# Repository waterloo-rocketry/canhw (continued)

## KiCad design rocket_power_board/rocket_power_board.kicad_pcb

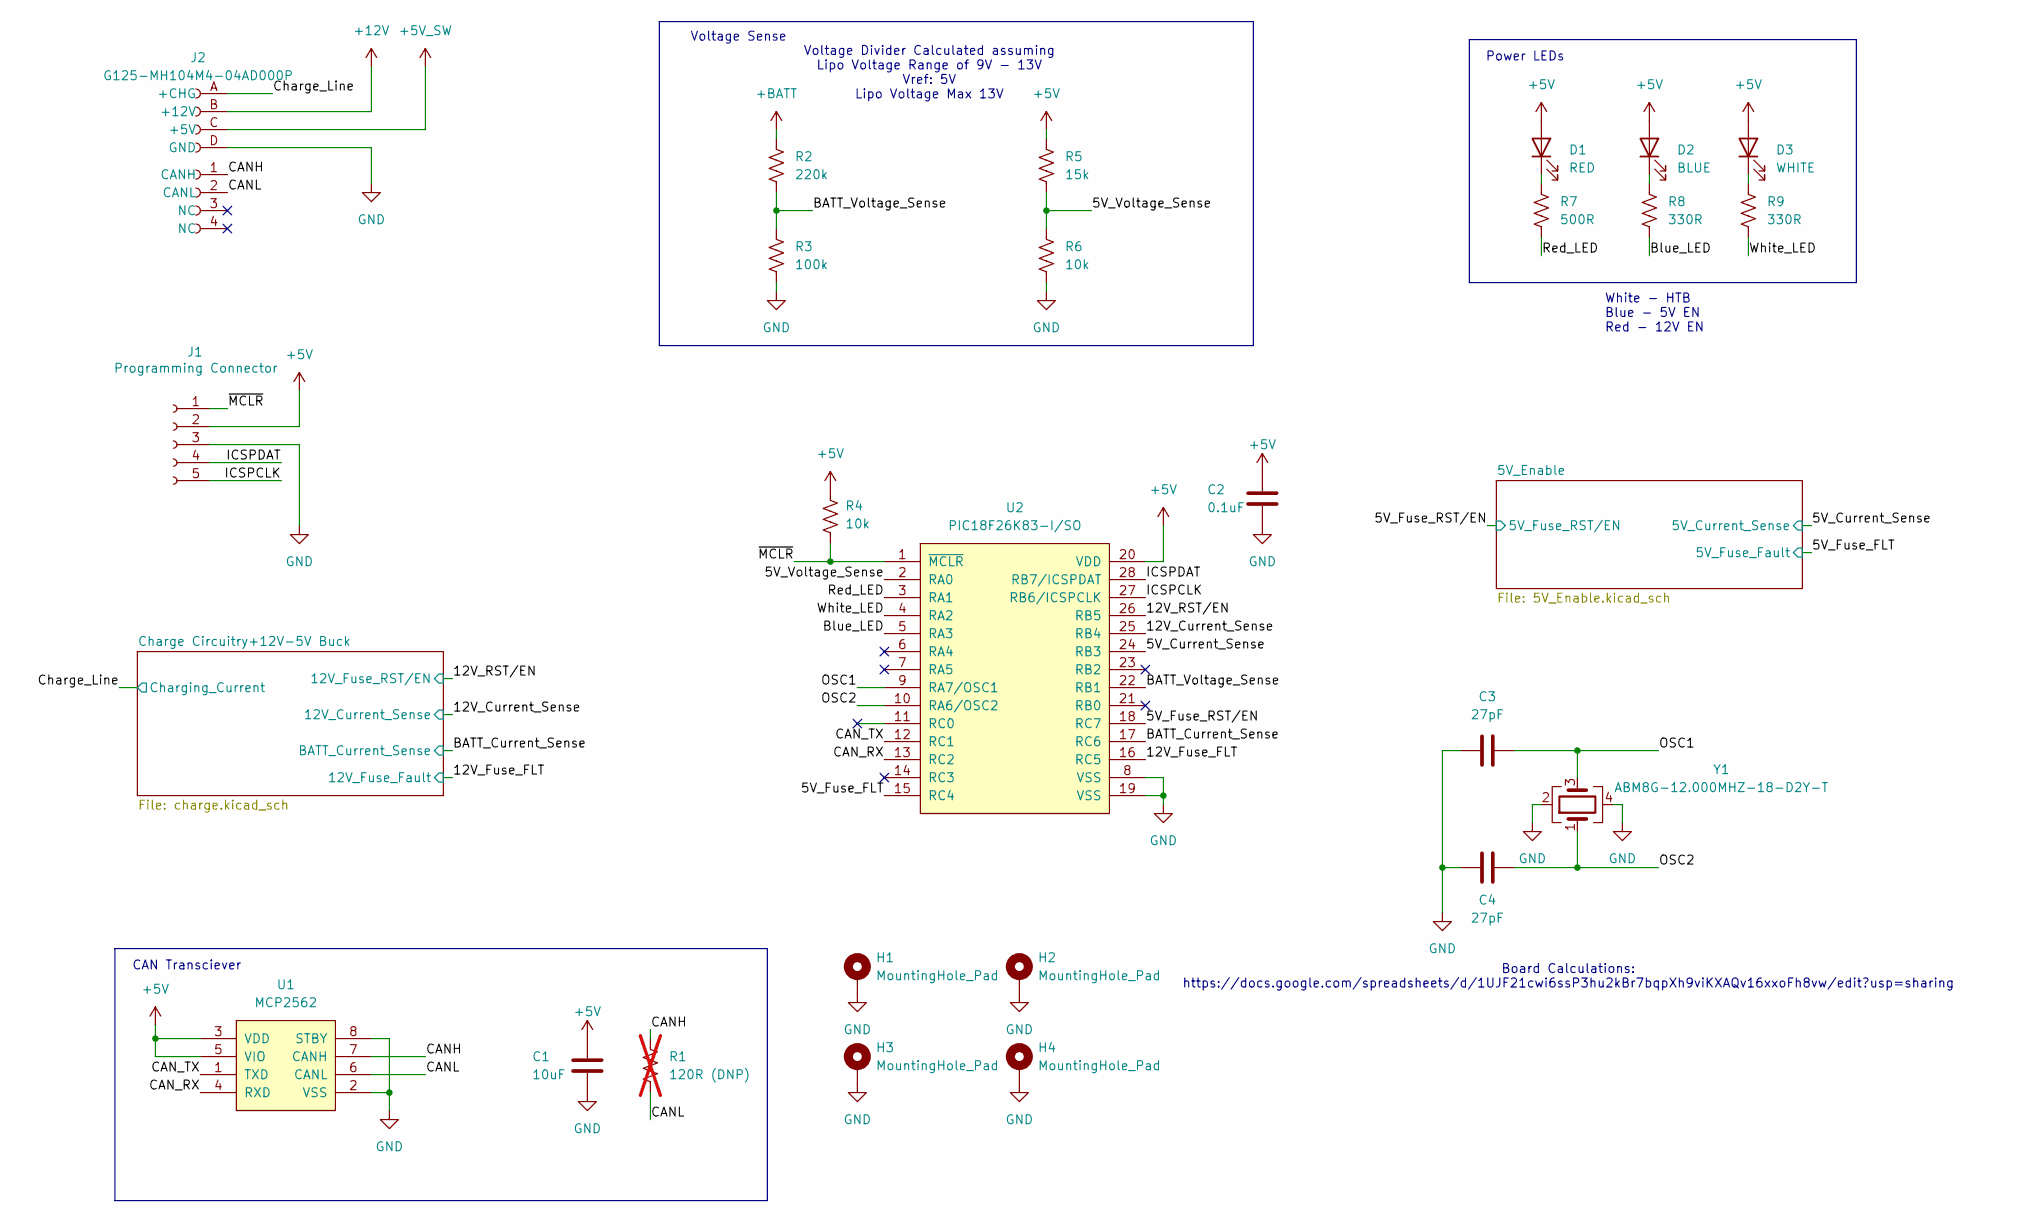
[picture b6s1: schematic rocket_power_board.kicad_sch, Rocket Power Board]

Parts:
C1: 10uF; C_0603_1608Metric_Pad1.08x0.95mm_HandSolder
C2: 0.1uF; C_0603_1608Metric_Pad1.08x0.95mm_HandSolder
C3, C4: 27pF; C_0603_1608Metric_Pad1.08x0.95mm_HandSolder
D1: RED; LED_1206_3216Metric_Pad1.42x1.75mm_HandSolder
D2: BLUE; LED_1206_3216Metric_Pad1.42x1.75mm_HandSolder
D3: WHITE; LED_1206_3216Metric_Pad1.42x1.75mm_HandSolder
H1, H2, H3, H4: MountingHole_Pad; MountingHole_3.2mm_M3_Pad_Via
J1: Programming Connector; PinSocket_5x2.54_SMD_90deg_952-3198-1-ND
J2: G125-MH104M4-04AD000P; connector_Harwin_G125-MH104M4-04AD000P
R1: 120R (DNP); R_0603_1608Metric_Pad0.98x0.95mm_HandSolder; not fitted
R2: 220k; R_0603_1608Metric_Pad0.98x0.95mm_HandSolder
R3: 100k; R_0603_1608Metric_Pad0.98x0.95mm_HandSolder
R4, R6: 10k; R_0603_1608Metric_Pad0.98x0.95mm_HandSolder
R5: 15k; R_0603_1608Metric_Pad0.98x0.95mm_HandSolder
R7: 500R; R_0603_1608Metric_Pad0.98x0.95mm_HandSolder
R8, R9: 330R; R_0603_1608Metric_Pad0.98x0.95mm_HandSolder
U1: MCP2562; SOIC-8_3.9x4.9mm_P1.27mm
U2: PIC18F26K83-I/SO; SOIC-28W_7.5x18.7mm_P1.27mm
Y1: ABM8G-12.000MHZ-18-D2Y-T; Crystal_SMD_Abracon_ABM8G-4Pin_3.2x2.5mm

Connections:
+5V: C1.1, C2.1, D1.2 (A), D2.2 (A), D3.2 (A), J1.2, R4.1, R5.1, U1.3 (VDD), U1.5 (VIO), U2.20 (VDD); also elsewhere on the board
+5V_SW: J2.C (+5V); also elsewhere on the board
+12V: J2.B (+12V); also elsewhere on the board
+BATT: R2.1; also elsewhere on the board
/5V_Current_Sense: U2.24 (RB3); also elsewhere on the board
/5V_Fuse_FLT: U2.15 (RC4); also elsewhere on the board
/5V_Fuse_RST/EN: U2.18 (RC7); also elsewhere on the board
/5V_Voltage_Sense: R5.2, R6.2, U2.2 (RA0)
/12V_Current_Sense: U2.25 (RB4); also elsewhere on the board
/12V_Fuse_FLT: U2.16 (RC5); also elsewhere on the board
/12V_RST/EN: U2.26 (RB5); also elsewhere on the board
/BATT_Current_Sense: U2.17 (RC6); also elsewhere on the board
/BATT_Voltage_Sense: R2.2, R3.2, U2.22 (RB1)
/Blue_LED: R8.2, U2.5 (RA3)
/CANH: J2.1 (CANH), R1.1, U1.7 (CANH)
/CANL: J2.2 (CANL), R1.2, U1.6 (CANL)
/CAN_RX: U1.4 (RXD), U2.13 (RC2)
/CAN_TX: U1.1 (TXD), U2.12 (RC1)
/Charge_Line: J2.A (+CHG); also elsewhere on the board
/ICSPCLK: J1.5, U2.27 (RB6/ICSPCLK)
/ICSPDAT: J1.4, U2.28 (RB7/ICSPDAT)
/OSC1: C3.2, U2.9 (RA7/OSC1), Y1.3
/OSC2: C4.2, U2.10 (RA6/OSC2), Y1.1
/Red_LED: R7.2, U2.3 (RA1)
/White_LED: R9.2, U2.4 (RA2)
/~MCLR: J1.1, R4.2, U2.1 (~MCLR)
GND: C1.2, C2.2, C3.1, C4.1, H1.1, H2.1, H3.1, H4.1, J1.3, J2.D (GND), R3.1, R6.1, U1.2 (VSS), U1.8 (STBY), U2.8 (VSS), U2.19 (VSS), Y1.2, Y1.4; also elsewhere on the board
unnamed: D1.1 (K), R7.1
unnamed: D2.1 (K), R8.1
unnamed: D3.1 (K), R9.1

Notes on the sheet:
Voltage Divider Calculated assuming Lipo Voltage Range of 9V - 13V Vref: 5V Lipo Voltage Max 13V
CAN Transciever
Board Calculations: https://docs.google.com/spreadsheets/d/1UJF21cwi6ssP3hu2kBr7bqpXh9viKXAQv16xxoFh8vw/edit?usp=sharing
White - HTB Blue - 5V EN Red - 12V EN
Power LEDs
Voltage Sense

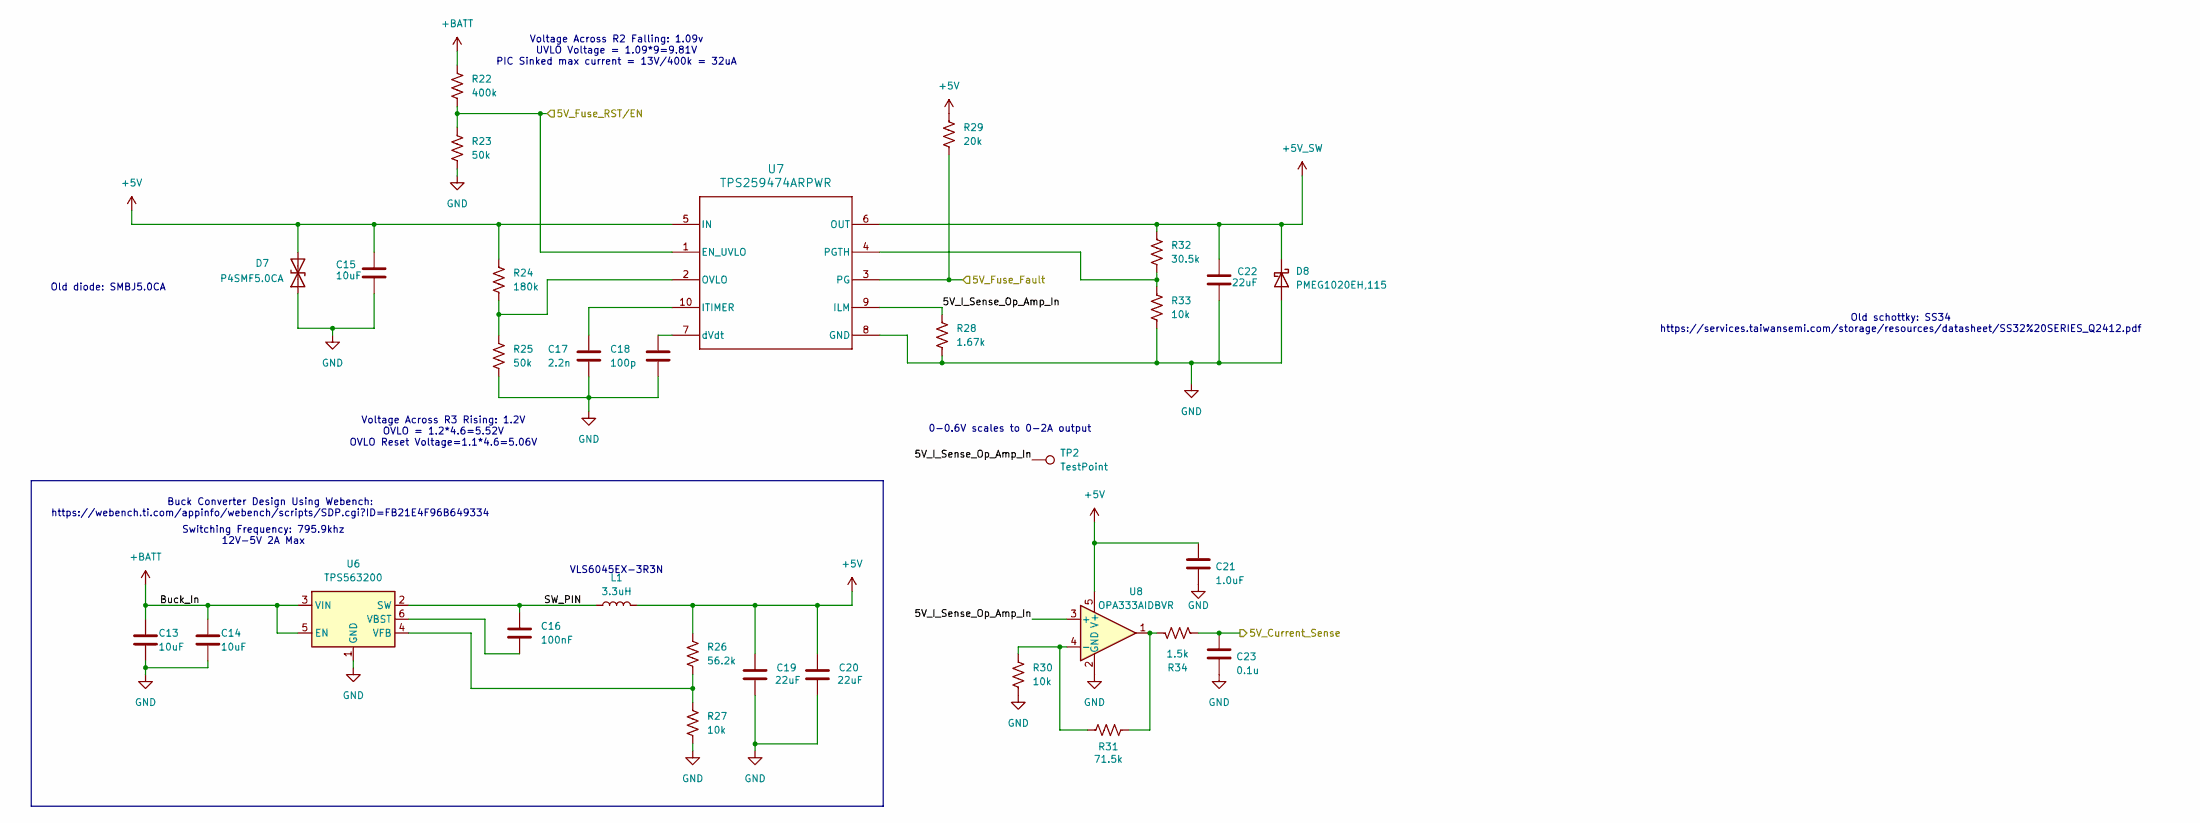
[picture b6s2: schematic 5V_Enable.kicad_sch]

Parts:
C13, C14, C15: 10uF; C_0603_1608Metric_Pad1.08x0.95mm_HandSolder
C16: 100nF; C_0603_1608Metric_Pad1.08x0.95mm_HandSolder
C17: 2.2n; C_0603_1608Metric_Pad1.08x0.95mm_HandSolder
C18: 100p; C_0603_1608Metric_Pad1.08x0.95mm_HandSolder
C19, C20: 22uF; LED_0805_2012Metric_Pad1.15x1.40mm_HandSolder
C21: 1.0uF; C_0603_1608Metric_Pad1.08x0.95mm_HandSolder
C22: 22uF; C_0805_2012Metric_Pad1.18x1.45mm_HandSolder
C23: 0.1u; C_0603_1608Metric_Pad1.08x0.95mm_HandSolder
D7: P4SMF5.0CA; D_SOD-123F
D8: PMEG1020EH,115; D_SOD-123F
L1: 3.3uH; IND_VLS6045EX-3R3N
R22: 400k; R_0603_1608Metric_Pad0.98x0.95mm_HandSolder
R23, R25: 50k; R_0603_1608Metric_Pad0.98x0.95mm_HandSolder
R24: 180k; R_0603_1608Metric_Pad0.98x0.95mm_HandSolder
R26: 56.2k; R_0603_1608Metric_Pad0.98x0.95mm_HandSolder
R27, R30, R33: 10k; R_0603_1608Metric_Pad0.98x0.95mm_HandSolder
R28: 1.67k; R_0603_1608Metric_Pad0.98x0.95mm_HandSolder
R29: 20k; R_0603_1608Metric_Pad0.98x0.95mm_HandSolder
R31: 71.5k; R_0603_1608Metric_Pad0.98x0.95mm_HandSolder
R32: 30.5k; R_0603_1608Metric_Pad0.98x0.95mm_HandSolder
R34: 1.5k; R_0603_1608Metric_Pad0.98x0.95mm_HandSolder
TP2: TestPoint; TestPoint_Pad_1.0x1.0mm
U6: TPS563200; SOT-23-6
U7: TPS259474ARPWR; Texas_RPW0010A_VQFN-10_2x2mm
U8: OPA333AIDBVR; SOT-23-5

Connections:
+5V: C15.1, C19.1, C20.1, C21.1, D7.2 (A2), L1.2, R24.1, R26.1, R29.1, U7.5 (IN), U8.5 (V+); also elsewhere on the board
+5V_SW: C22.1, D8.1 (K), R32.1, U7.6 (OUT); also elsewhere on the board
+BATT: C13.1, C14.1, R22.1, U6.3 (VIN), U6.5 (EN); also elsewhere on the board
/5V_Current_Sense: C23.1, R34.1; also elsewhere on the board
/5V_Enable/5V_I_Sense_Op_Amp_In: R28.1, TP2.1, U7.9 (ILM), U8.3 (+); also elsewhere on the board
/5V_Enable/SW_PIN: C16.1, L1.1, U6.2 (SW)
/5V_Fuse_FLT: R29.2, U7.3 (PG); also elsewhere on the board
/5V_Fuse_RST/EN: R22.2, R23.1, U7.1 (EN_UVLO); also elsewhere on the board
GND: C13.2, C14.2, C15.2, C17.2, C18.2, C19.2, C20.2, C21.2, C22.2, C23.2, D7.1 (A1), D8.2 (A), R23.2, R25.2, R27.2, R28.2, R30.2, R33.2, U6.1 (GND), U7.8 (GND), U8.2 (GND); also elsewhere on the board
unnamed: R31.2, R34.2, U8.1
unnamed: C16.2, U6.6 (VBST)
unnamed: R26.2, R27.1, U6.4 (VFB)
unnamed: C17.1, U7.10 (ITIMER)
unnamed: R24.2, R25.1, U7.2 (OVLO)
unnamed: R32.2, R33.1, U7.4 (PGTH)
unnamed: C18.1, U7.7 (dVdt)
unnamed: R30.1, R31.1, U8.4 (-)

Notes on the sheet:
Switching Frequency: 795.9khz 12V-5V 2A Max
VLS6045EX-3R3N
0-0.6V scales to 0-2A output
Buck Converter Design Using Webench: https://webench.ti.com/appinfo/webench/scripts/SDP.cgi?ID=FB21E4F96B649334
Old schottky: SS34 https://services.taiwansemi.com/storage/resources/datasheet/SS32%20SERIES_Q2412.pdf
Voltage Across R2 Falling: 1.09v UVLO Voltage = 1.09*9=9.81V PIC Sinked max current = 13V/400k = 32uA
Old diode: SMBJ5.0CA
Voltage Across R3 Rising: 1.2V OVLO = 1.2*4.6=5.52V OVLO Reset Voltage=1.1*4.6=5.06V

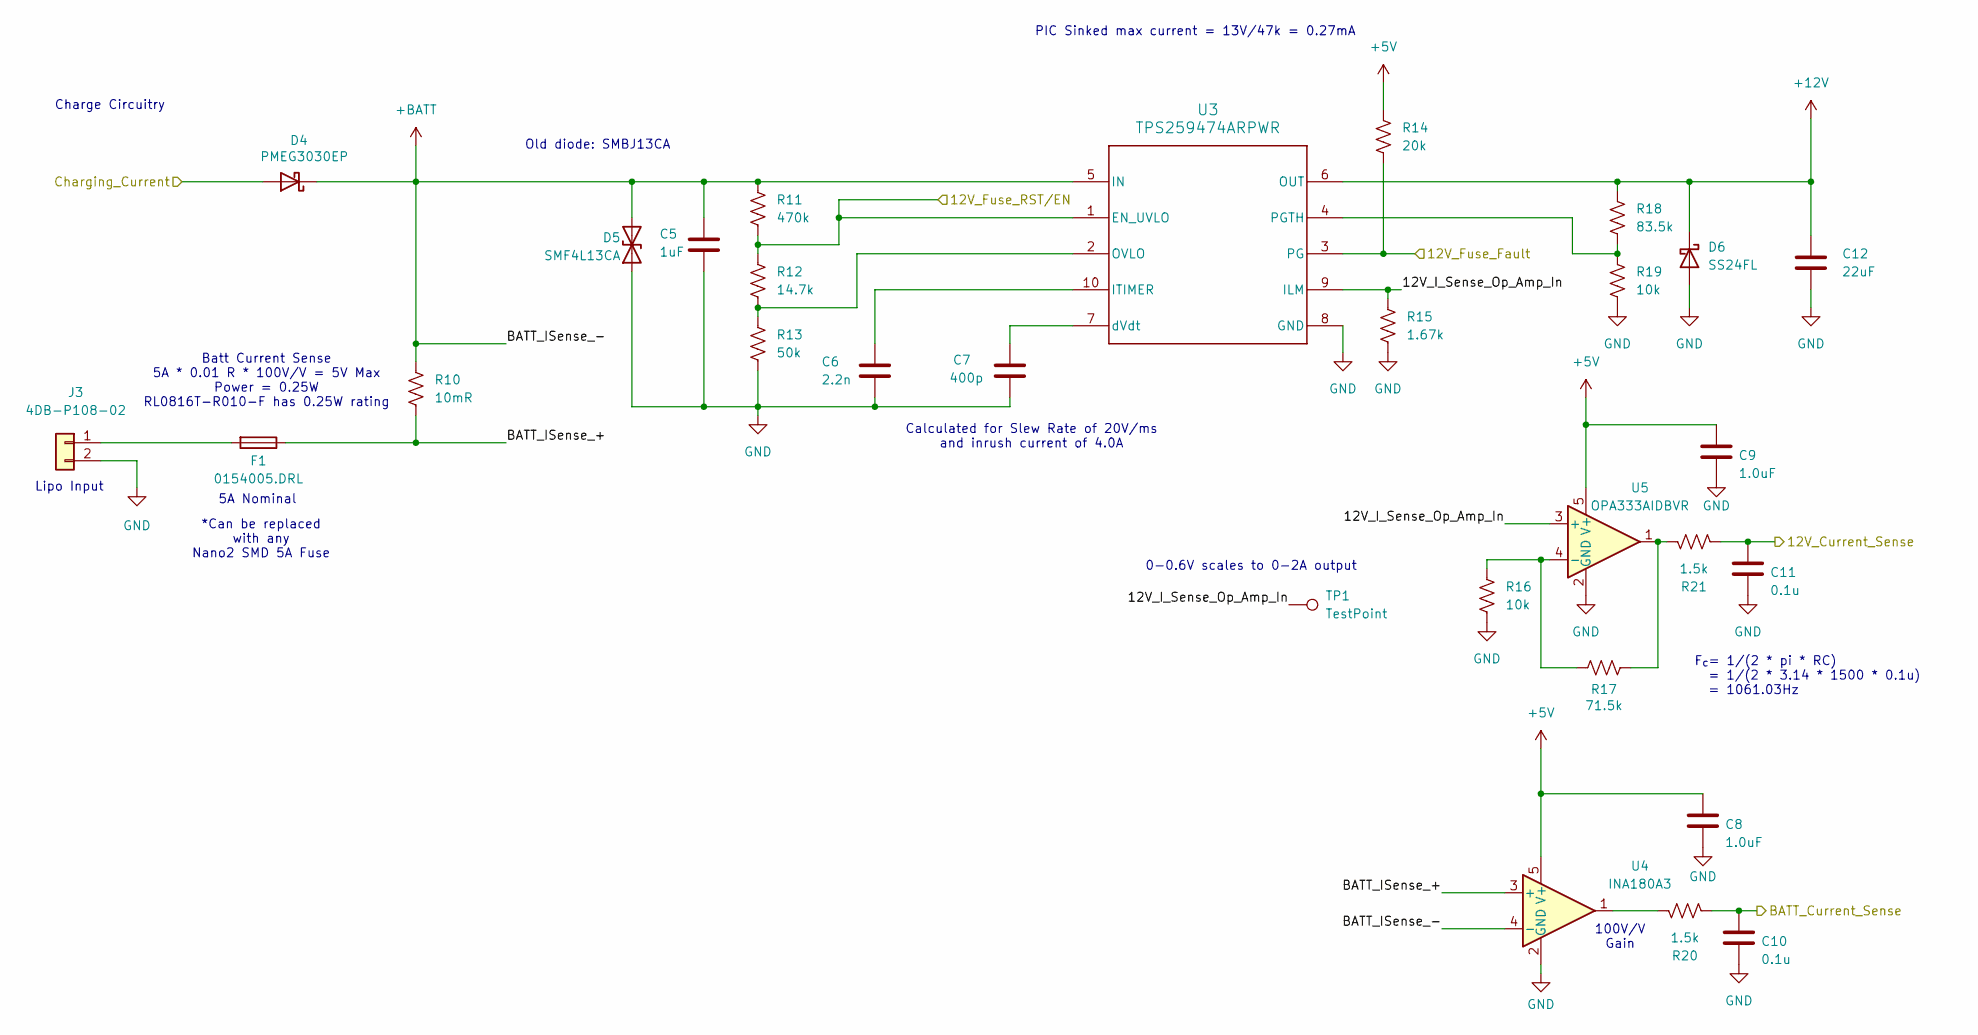
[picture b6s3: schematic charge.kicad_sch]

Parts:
C5: 1uF; C_0603_1608Metric_Pad1.08x0.95mm_HandSolder
C6: 2.2n; C_0603_1608Metric_Pad1.08x0.95mm_HandSolder
C7: 400p; C_0603_1608Metric_Pad1.08x0.95mm_HandSolder
C8, C9: 1.0uF; C_0603_1608Metric_Pad1.08x0.95mm_HandSolder
C10, C11: 0.1u; C_0603_1608Metric_Pad1.08x0.95mm_HandSolder
C12: 22uF; C_0805_2012Metric_Pad1.18x1.45mm_HandSolder
D4: PMEG3030EP; D_SOD-128
D5: SMF4L13CA; D_SOD-123F
D6: SS24FL; D_SOD-123F
F1: 0154005.DRL; 0154Series_LTF
J3: 4DB-P108-02; TE_2-1437667-4
R10: 10mR; R_0603_1608Metric_Pad0.98x0.95mm_HandSolder
R11: 470k; R_0603_1608Metric_Pad0.98x0.95mm_HandSolder
R12: 14.7k; R_0603_1608Metric_Pad0.98x0.95mm_HandSolder
R13: 50k; R_0603_1608Metric_Pad0.98x0.95mm_HandSolder
R14: 20k; R_0603_1608Metric_Pad0.98x0.95mm_HandSolder
R15: 1.67k; R_0603_1608Metric_Pad0.98x0.95mm_HandSolder
R16, R19: 10k; R_0603_1608Metric_Pad0.98x0.95mm_HandSolder
R17: 71.5k; R_0603_1608Metric_Pad0.98x0.95mm_HandSolder
R18: 83.5k; R_0603_1608Metric_Pad0.98x0.95mm_HandSolder
R20, R21: 1.5k; R_0603_1608Metric_Pad0.98x0.95mm_HandSolder
TP1: TestPoint; TestPoint_Pad_1.0x1.0mm
U3: TPS259474ARPWR; Texas_RPW0010A_VQFN-10_2x2mm
U4: INA180A3; SOT-23-5
U5: OPA333AIDBVR; SOT-23-5

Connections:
+5V: C8.1, C9.1, R14.1, U4.5 (V+), U5.5 (V+); also elsewhere on the board
+12V: C12.1, D6.1 (K), R18.1, U3.6 (OUT); also elsewhere on the board
+BATT: C5.1, D4.1 (K), D5.2 (A2), R10.1, R11.1, U3.5 (IN), U4.4 (-); also elsewhere on the board
/12V_Current_Sense: C11.1, R21.1; also elsewhere on the board
/12V_Fuse_FLT: R14.2, U3.3 (PG); also elsewhere on the board
/12V_RST/EN: R11.2, R12.1, U3.1 (EN_UVLO); also elsewhere on the board
/BATT_Current_Sense: C10.1, R20.1; also elsewhere on the board
/Charge Circuitry+12V-5V Buck/12V_I_Sense_Op_Amp_In: R15.1, TP1.1, U3.9 (ILM), U5.3 (+); also elsewhere on the board
/Charge Circuitry+12V-5V Buck/BATT_ISense_+: F1.1, R10.2, U4.3 (+)
/Charge_Line: D4.2 (A); also elsewhere on the board
GND: C5.2, C6.2, C7.2, C8.2, C9.2, C10.2, C11.2, C12.2, D5.1 (A1), D6.2 (A), J3.2, R13.2, R15.2, R16.2, R19.2, U3.8 (GND), U4.2 (GND), U5.2 (GND); also elsewhere on the board
unnamed: F1.2, J3.1
unnamed: R17.2, R21.2, U5.1
unnamed: R20.2, U4.1
unnamed: C6.1, U3.10 (ITIMER)
unnamed: R12.2, R13.1, U3.2 (OVLO)
unnamed: R18.2, R19.1, U3.4 (PGTH)
unnamed: C7.1, U3.7 (dVdt)
unnamed: R16.1, R17.1, U5.4 (-)

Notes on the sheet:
Charge Circuitry
100V/V Gain
F_{c}= 1/(2 * pi * RC) = 1/(2 * 3.14 * 1500 * 0.1u) = 1061.03Hz
0-0.6V scales to 0-2A output
Old diode: SMBJ13CA
Calculated for Slew Rate of 20V/ms and inrush current of 4.0A
*Can be replaced with any Nano2 SMD 5A Fuse
Lipo Input
PIC Sinked max current = 13V/47k = 0.27mA
5A Nominal
Batt Current Sense 5A * 0.01 R * 100V/V = 5V Max Power = 0.25W RL0816T-R010-F has 0.25W rating

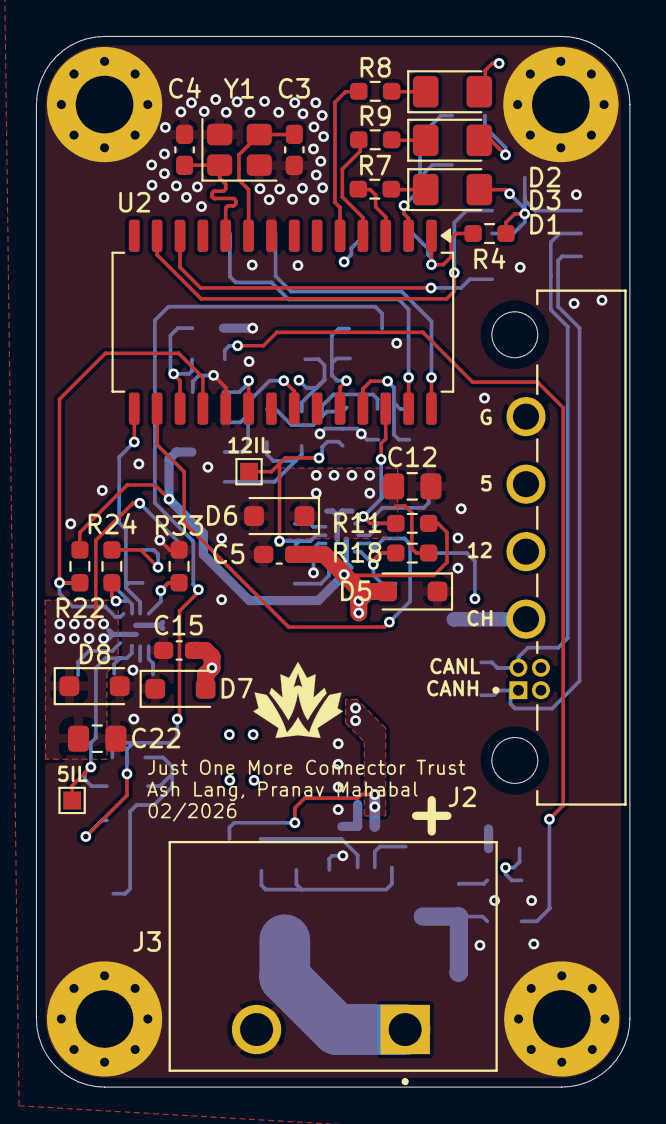
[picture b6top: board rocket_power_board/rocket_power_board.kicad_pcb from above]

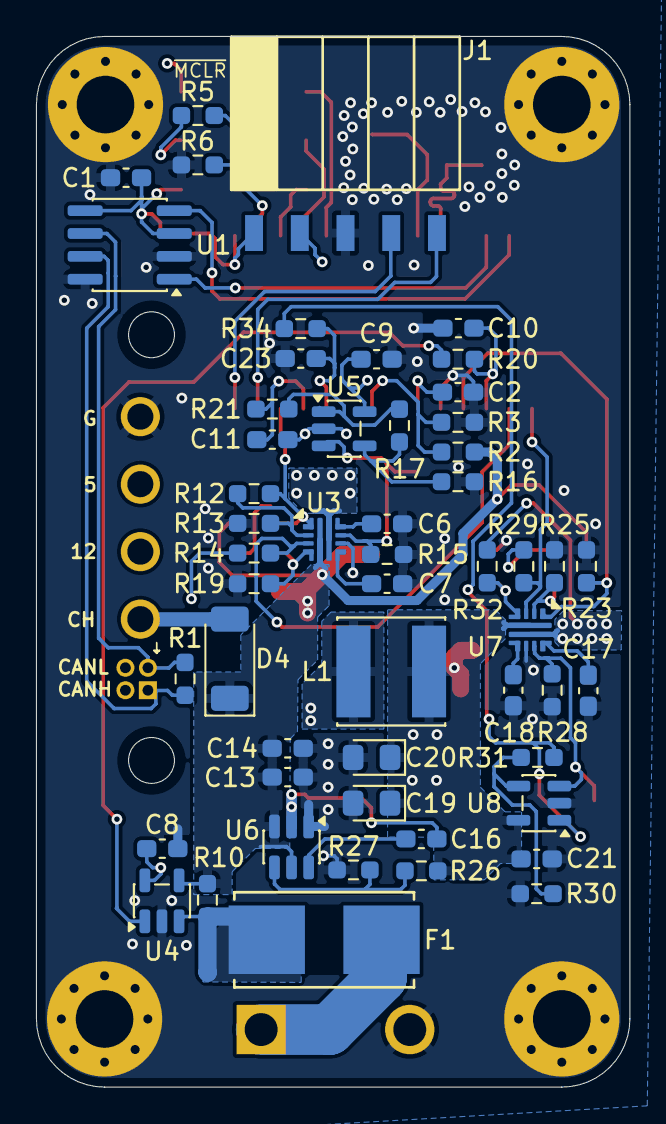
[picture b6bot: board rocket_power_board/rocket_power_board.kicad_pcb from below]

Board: 4 copper layers, 33.0 x 58.4 mm, 85 parts (53 on the bottom side), 50 nets.

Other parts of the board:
5IL, 12IL: TestPoint; TestPoint_Pad_1.0x1.0mm

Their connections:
/5V_Enable/5V_I_Sense_Op_Amp_In: 5IL.1; also elsewhere on the board
/Charge Circuitry+12V-5V Buck/12V_I_Sense_Op_Amp_In: 12IL.1; also elsewhere on the board

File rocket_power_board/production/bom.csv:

Designator,Footprint,Quantity,Value,LCSC Part #
"12IL, 5IL",TestPoint_Pad_1.0x1.0mm,2,TestPoint,
"C1, C13, C14, C15",0603,4,10uF,
"C10, C11, C23",0603,3,0.1u,
"C12, C19, C20, C22",0805,4,22uF,
C16,0603,1,100nF,
"C17, C6",0603,2,2.2n,
C18,0603,1,100p,
C2,0603,1,0.1uF,
"C21, C8, C9",0603,3,1.0uF,
"C3, C4",0603,2,27pF,
C5,0603,1,1uF,
C7,0603,1,100pF,
D1,1206,1,RED,
D2,1206,1,BLUE,
D3,1206,1,WHITE,
D4,D_SOD-128,1,PMEG3030EP,
D5,D_SOD-123F,1,SMF4L13CA,
D6,D_SOD-123F,1,SS24FL,
D7,D_SOD-123F,1,P4SMF5.0CA,
D8,D_SOD-123F,1,"PMEG1020EH,115",
F1,0154Series_LTF,1,0154005.DRL,
J1,PinSocket_5x2.54_SMD_90deg_952-3198-1-ND,1,Programming Connector,
J2,connector_Harwin_G125-MH104M4-04AD000P,1,G125-MH104M4-04AD000P,
J3,TE_2-1437667-4,1,4DB-P108-02,
L1,IND_VLS6045EX-3R3N,1,3.3uH,
R1,0603,1,120R (DNP),
R10,0603,1,10mR,
R11,0603,1,470k,
R12,0603,1,14.7k,
"R13, R23, R25",0603,3,50k,
"R14, R29",0603,2,20k,
"R15, R28",0603,2,1.67k,
"R16, R19, R27, R30, R33, R4, R6",0603,7,10k,
"R17, R31",0603,2,71.5k,
R18,0603,1,83.5k,
R2,0603,1,220k,
"R20, R21, R34",0603,3,1.5k,
R22,0603,1,400k,
R24,0603,1,180k,
R26,0603,1,56.2k,
R3,0603,1,100k,
R32,0603,1,30.5k,
R5,0603,1,15k,
R7,0603,1,500R,
"R8, R9",0603,2,330R,
U1,SOIC-8_3.9x4.9mm_P1.27mm,1,MCP2562,
U2,SOIC-28W_7.5x18.7mm_P1.27mm,1,PIC18F26K83-I/SO,
"U3, U7",Texas_RPW0010A_VQFN-10_2x2mm,2,TPS259474ARPWR,
U4,SOT-23-5,1,INA180A3,
"U5, U8",SOT-23-5,2,OPA333AIDR,
U6,SOT-23-6,1,TPS563200,
Y1,Crystal_SMD_Abracon_ABM8G-4Pin_3.2x2.5mm,1,ABM8G-12.000MHZ-18-D2Y-T,

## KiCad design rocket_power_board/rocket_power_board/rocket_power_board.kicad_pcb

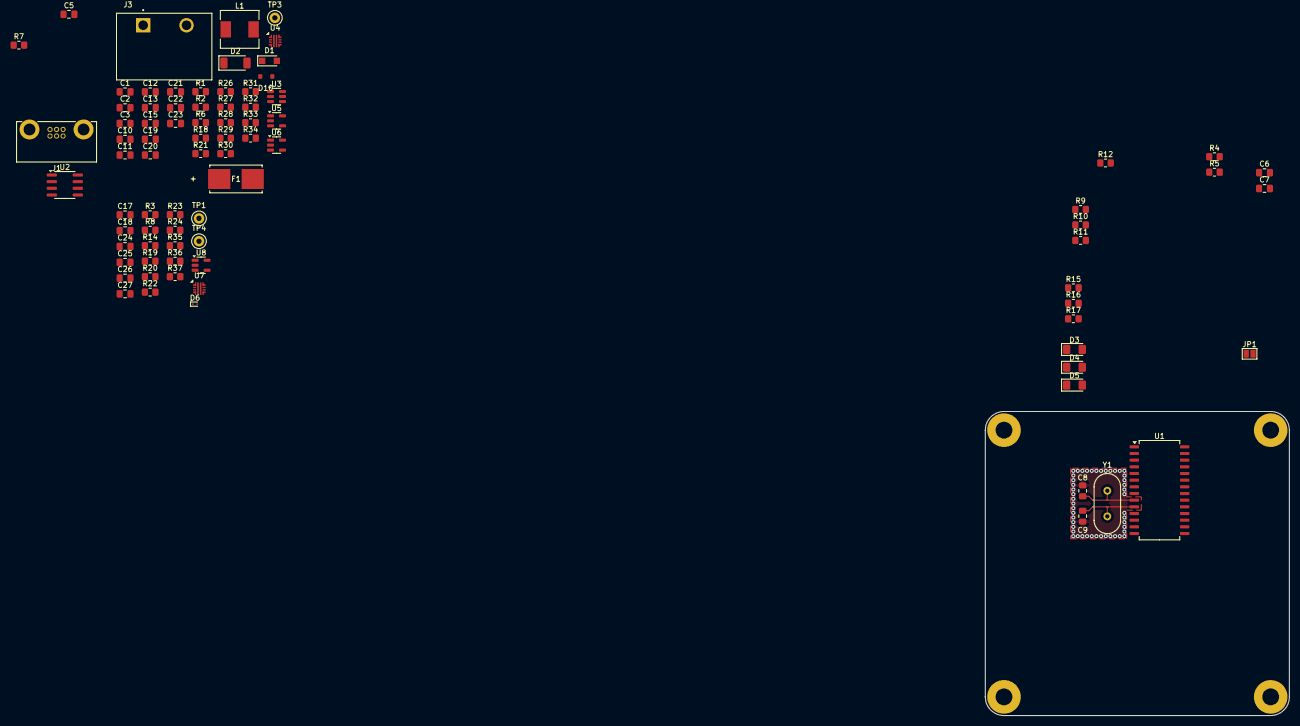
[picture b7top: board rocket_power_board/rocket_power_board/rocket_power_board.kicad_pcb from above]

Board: 4 copper layers, 57.9 x 57.9 mm, 88 parts (1 on the bottom side), 53 nets.

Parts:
C1, C3, C5: 10uF; C_0805_2012Metric_Pad1.18x1.45mm_HandSolder
C2, C13: 22uF; C_0805_2012Metric_Pad1.18x1.45mm_HandSolder
C6, C7: 0.1uF; C_0805_2012Metric_Pad1.18x1.45mm_HandSolder
C8, C9: 27pF; C_0805_2012Metric_Pad1.18x1.45mm_HandSolder
C10, C23, C27: 1.6nF; C_0805_2012Metric_Pad1.18x1.45mm_HandSolder
C11, C22, C26: 1.0uF; C_0805_2012Metric_Pad1.18x1.45mm_HandSolder
C12: 100nF; C_0805_2012Metric_Pad1.18x1.45mm_HandSolder
C15, C17, C19, C25: 1uF; C_0805_2012Metric_Pad1.18x1.45mm_HandSolder
C18: 100pF; C_0805_2012Metric_Pad1.18x1.45mm_HandSolder
C20: 200pF; C_0805_2012Metric_Pad1.18x1.45mm_HandSolder
C21, C24: F; C_0805_2012Metric_Pad1.18x1.45mm_HandSolder
D1: PMEG2010ER; Nexperia_CFP3_SOD-123W
D2: PMEG3030EP; D_SOD-128
D3: RED; LED_1206_3216Metric_Pad1.42x1.75mm_HandSolder
D4: BLUE; LED_1206_3216Metric_Pad1.42x1.75mm_HandSolder
D5: WHITE; LED_1206_3216Metric_Pad1.42x1.75mm_HandSolder
D6: D5V0F1U2S9-7; D_SOD-923
D10: DF2S14P2FU
F1: 0154005.DRL; 0154Series_LTF
H1, H2, H3, H4: MountingHole_Pad; MountingHole_3.2mm_M3_Pad
J1: Harwin_G125–MH10605M4P; connector_Harwin_G125–MG10605M4P
J2: Programming Connector; PinSocket_5x2.54_SMD_90deg_952-3198-1-ND
J3: 4DB-P108-02; TE_2-1437667-4
JP1: Solder Jumper; SolderJumper-2_P1.3mm_Open_Pad1.0x1.5mm
L1: 3.3uH; L_Wuerth_HCM-7050
R1: 56.2k; R_0805_2012Metric_Pad1.20x1.40mm_HandSolder
R2, R4, R12, R22, R29, R34, R35: 10k; R_0805_2012Metric_Pad1.20x1.40mm_HandSolder
R3: 180k; R_0805_2012Metric_Pad1.20x1.40mm_HandSolder
R5, R16, R17: 120R; R_0805_2012Metric_Pad1.20x1.40mm_HandSolder
R6: 10mR; R_0805_2012Metric_Pad1.20x1.40mm_HandSolder
R7: 120R (DNP); R_0805_2012Metric_Pad1.20x1.40mm_HandSolder
R8, R24, R27: 50k; R_0805_2012Metric_Pad1.20x1.40mm_HandSolder
R9: 220k; R_0805_2012Metric_Pad1.20x1.40mm_HandSolder
R10: 100k; R_0805_2012Metric_Pad1.20x1.40mm_HandSolder
R11: 15k; R_0805_2012Metric_Pad1.20x1.40mm_HandSolder
R14, R28: 1.67k; R_0805_2012Metric_Pad1.20x1.40mm_HandSolder
R15: 220R; R_0805_2012Metric_Pad1.20x1.40mm_HandSolder
R18, R31, R37: 500R; R_0805_2012Metric_Pad1.20x1.40mm_HandSolder
R19, R33: 20k; R_0805_2012Metric_Pad1.20x1.40mm_HandSolder
R20: 30.5k; R_0805_2012Metric_Pad1.20x1.40mm_HandSolder
R21: 47k; R_0805_2012Metric_Pad1.20x1.40mm_HandSolder
R23: 400k; R_0805_2012Metric_Pad1.20x1.40mm_HandSolder
R26: 14.7k; R_0805_2012Metric_Pad1.20x1.40mm_HandSolder
R30, R36: 71.5k; R_0805_2012Metric_Pad1.20x1.40mm_HandSolder
R32: 83.5k; R_0805_2012Metric_Pad1.20x1.40mm_HandSolder
TP1: 5V; TestPoint_Keystone_5000-5004_Miniature
TP3: 12V_Voltage; TestPoint_Keystone_5000-5004_Miniature
TP4: 5V_SW; TestPoint_Keystone_5000-5004_Miniature
U1: PIC18F26K83-I/SO; SOIC-28W_7.5x18.7mm_P1.27mm
U2: MCP2562; SOIC-8_3.9x4.9mm_P1.27mm
U3: TPS563200; SOT-23-6
U4, U7: TPS259474ARPWR; Texas_RPW0010A_VQFN-10_2x2mm
U5, U8: INA180A1; SOT-23-5
U6: INA180A3; SOT-23-5
Y1: 12 MHz; Crystal_HC49-4H_Vertical

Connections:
+5V: C2.1, C5.1, C6.1, C11.1, C13.1, C17.1, C22.1, C26.1, D3.2 (A), D4.2 (A), D5.2 (A), D6.2 (A2), J2.4, L1.2, R1.1, R3.1, R4.1, R11.1, R19.1, R33.1, TP1.1, U1.20 (VDD), U2.3 (VDD), U2.5 (VIO), U5.5 (V+), U6.5 (V+), U7.5 (IN), U8.5 (V+)
+5V_SW: C25.1, J1.5, R20.1, TP4.1, U7.6 (OUT)
+12V: C15.1, J1.6, R32.1, TP3.1, U4.6 (OUT)
+BATT: C19.1, D1.1 (K), D2.2 (A), D10.2 (A2), F1.2, R9.1, R21.1, R23.1, U4.5 (IN)
/5V_Current_Sense: C27.1, R37.1, U1.24 (RB3)
/5V_Enable/5V_I_Sense_Op_Amp_In: R14.1, U7.9 (ILM), U8.3 (+)
/5V_Fuse_FLT: R19.2, U1.15 (RC4), U7.3 (PG)
/5V_Fuse_RST/EN: R23.2, R24.1, U1.18 (RC7), U7.1 (EN_UVLO)
/5V_Voltage_Sense: R11.2, R12.2, U1.2 (RA0)
/12V_Current_Sense: C23.1, R31.1, U1.25 (RB4)
/12V_Fuse_FLT: R33.2, U1.16 (RC5), U4.3 (PG)
/12V_RST/EN: R21.2, R26.1, U1.21 (RB0), U4.1 (EN_UVLO)
/BATT_Current_Sense: C10.1, R18.1, U1.17 (RC6)
/BATT_Voltage_Sense: R9.2, R10.2, U1.22 (RB1)
/Blue_LED: R16.2, U1.12 (RC1)
/CANH: J1.3, R7.1, U2.7 (CANH)
/CANL: J1.2, R7.2, U2.6 (CANL)
/CAN_RX: U1.3 (RA1), U2.4 (RXD)
/CAN_TX: U1.4 (RA2), U2.1 (TXD)
/Charge Circuitry+12V-5V Buck/12V_I_Sense_Op_Amp_In: R28.1, U4.9 (ILM), U5.3 (+)
/Charge Circuitry+12V-5V Buck/BATT_ISense_+: J3.2, R6.2, U6.3 (+)
/Charge Circuitry+12V-5V Buck/BATT_ISense_-: F1.1, R6.1, U6.4 (-)
/Charge Circuitry+12V-5V Buck/Buck_In: C1.1, C3.1, D2.1 (K), U3.3 (VIN), U3.5 (EN)
/Charge Circuitry+12V-5V Buck/SW_PIN: C12.1, L1.1, U3.2 (SW)
/Charge_Line: D1.2 (A), J1.1
/ICSPCLK: J2.1, U1.27 (RB6/ICSPCLK)
/ICSPDAT: J2.2, U1.28 (RB7/ICSPDAT)
/OSC1: C8.2, U1.9 (RA7/OSC1), Y1.2
/OSC2: C9.2, U1.10 (RA6/OSC2), Y1.1
/Red_LED: R15.2, U1.13 (RC2)
/White_LED: R17.2, U1.14 (RC3)
/~MCLR: J2.5, JP1.2 (B), R4.2, R5.2
GND: C1.2, C2.2, C3.2, C5.2, C6.2, C7.2, C8.1, C9.1, C10.2, C11.2, C13.2, C15.2, C17.2, C18.2, C19.2, C20.2, C21.2, C22.2, C23.2, C24.2, C25.2, C26.2, C27.2, D6.1 (A1), D10.1 (A1), H1.1, H2.1, H3.1, H4.1, J1.4, J2.3, J3.1, R2.2, R8.2, R10.1, R12.1, R14.2, R22.2, R24.2, R27.2, R28.2, R29.2, R34.2, R35.2, U1.8 (VSS), U1.19 (VSS), U2.2 (VSS), U2.8 (STBY), U3.1 (GND), U4.8 (GND), U5.2 (GND), U6.2 (GND), U7.8 (GND), U8.2 (GND)
unnamed: D3.1 (K), R15.1
unnamed: D4.1 (K), R16.1
unnamed: D5.1 (K), R17.1
unnamed: C7.1, JP1.1 (A)
unnamed: R18.2, U6.1
unnamed: R30.2, R31.2, U5.1
unnamed: R36.2, R37.2, U8.1
unnamed: R5.1, U1.1 (~MCLR)
unnamed: C12.2, U3.6 (VBST)
unnamed: R1.2, R2.1, U3.4 (VFB)
unnamed: C21.1, U4.10 (ITIMER)
unnamed: R26.2, R27.1, U4.2 (OVLO)
unnamed: R32.2, R34.1, U4.4 (PGTH)
unnamed: C20.1, U4.7 (dVdt)
unnamed: R29.1, R30.1, U5.4 (-)
unnamed: C24.1, U7.10 (ITIMER)
unnamed: R3.2, R8.1, U7.2 (OVLO)
unnamed: R20.2, R22.1, U7.4 (PGTH)
unnamed: C18.1, U7.7 (dVdt)
unnamed: R35.1, R36.1, U8.4 (-)

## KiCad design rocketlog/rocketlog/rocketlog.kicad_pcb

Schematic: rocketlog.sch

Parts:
C1, C2: 0.1u; C_0805_2012Metric_Pad1.15x1.40mm_HandSolder
C3: 10u; C_0805_2012Metric_Pad1.15x1.40mm_HandSolder
C4, C5: C_Small; C_0805_2012Metric_Pad1.15x1.40mm_HandSolder
C11: C; C_0805_2012Metric_Pad1.15x1.40mm_HandSolder
D1: DEBUG1; LED_1206_3216Metric_Pad1.42x1.75mm_HandSolder
D2: DEBUG2; LED_1206_3216Metric_Pad1.42x1.75mm_HandSolder
J1: Conn_01x05_Female; PinHeader_5x2.54_SMD_90deg_952-3198-1-ND
R1: 10K; R_0805_2012Metric_Pad1.15x1.40mm_HandSolder
R3, R4: 330; R_0805_2012Metric_Pad1.15x1.40mm_HandSolder
U1: DSPIC33EP512GP502; SOIC-28W_7.5x17.9mm_P1.27mm
U2: MCP2562; SOIC-8_3.9x4.9mm_P1.27mm
Y1: Crystal; Crystal_SMD_0603-2Pin_6.0x3.5mm_HandSoldering

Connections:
+3V3: C1.1, C2.2, J1.4, R1.1, U1.13, U1.28, U2.5; also elsewhere on the board
+5V: C11.1, R3.1, R4.1, U2.3; also elsewhere on the board
/CANRX: U1.21, U2.4
/CANTX: U1.22, U2.1
/ICSPCLK: J1.1, U1.6
/ICSPDAT: J1.2, U1.7
/OSC1: C4.1, U1.9, Y1.1
/OSC2: C5.1, U1.10, Y1.2
/SD1_CS: U1.18; also elsewhere on the board
/SD1_MISO: U1.15; also elsewhere on the board
/SD1_MOSI: U1.17; also elsewhere on the board
/SD1_SCLK: U1.16; also elsewhere on the board
/SD2_CS: U1.4; also elsewhere on the board
/SD2_MISO: U1.14; also elsewhere on the board
/SD2_MOSI: U1.11; also elsewhere on the board
/SD2_SCLK: U1.12; also elsewhere on the board
/~MCLR: J1.5, R1.2, U1.1
CANH: U2.7; also elsewhere on the board
CANL: U2.6; also elsewhere on the board
CURR_AMP: U1.3; also elsewhere on the board
GND: C1.2, C2.1, C3.2, C4.2, C5.2, C11.2, J1.3, U1.8, U1.19, U1.27, U2.2, U2.8; also elsewhere on the board
unnamed: C3.1, U1.20
unnamed: D1.1, U1.24
unnamed: D1.2, R3.2
unnamed: D2.1, U1.25
unnamed: D2.2, R4.2

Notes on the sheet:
Not all pins support peripheral output, which is required for MOSI, SCK, and CANTX. RP20 and RP35-43 are the ones that support peripheral ouptut

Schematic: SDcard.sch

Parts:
C7: 4.7uF; C_0805_2012Metric_Pad1.15x1.40mm_HandSolder
J3: Micro_SD_Card; microSD_Molex_WM6698CT-ND
R2: R; R_0805_2012Metric_Pad1.15x1.40mm_HandSolder

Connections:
+3V3: C7.1, J3.4, R2.1; also elsewhere on the board
/SD1_MISO: R2.2; also elsewhere on the board
/SD2_CS: J3.2; also elsewhere on the board
/SD2_MISO: J3.7; also elsewhere on the board
/SD2_MOSI: J3.3; also elsewhere on the board
/SD2_SCLK: J3.5; also elsewhere on the board
GND: C7.2, J3.6; also elsewhere on the board

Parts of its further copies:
C6: 4.7uF; C_0805_2012Metric_Pad1.15x1.40mm_HandSolder
J2: Micro_SD_Card; microSD_Molex_WM6698CT-ND
R6: R; R_0805_2012Metric_Pad1.15x1.40mm_HandSolder

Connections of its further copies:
+3V3: C6.1, J2.4, R6.1; also elsewhere on the board
/SD1_CS: J2.2; also elsewhere on the board
/SD1_MISO: J2.7; also elsewhere on the board
/SD1_MOSI: J2.3; also elsewhere on the board
/SD1_SCLK: J2.5; also elsewhere on the board
/SD2_MISO: R6.2; also elsewhere on the board
GND: C6.2, J2.6; also elsewhere on the board

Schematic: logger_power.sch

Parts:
C8: 0.1u; C_0805_2012Metric_Pad1.15x1.40mm_HandSolder
C9, C10: 4.7u; C_0805_2012Metric_Pad1.15x1.40mm_HandSolder
F1: Polyfuse; Fuse_1206_3216Metric_Pad1.42x1.75mm_HandSolder
J4: BUS CONN; connector_Harwin_M80-5420642
R5: 62mOhm; R_0805_2012Metric_Pad1.15x1.40mm_HandSolder
U3: AP2114H-3.3; SOT-23-5_HandSoldering
U4: INA180; SOT-23-5_HandSoldering

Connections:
+3V3: C8.2, C9.2, U3.5 (VOUT), U4.5; also elsewhere on the board
+5V: C10.2, R5.1, U3.1 (VIN), U3.3 (EN), U4.4; also elsewhere on the board
CANH: J4.2; also elsewhere on the board
CANL: J4.1; also elsewhere on the board
CURR_AMP: U4.1; also elsewhere on the board
GND: C8.1, C9.1, C10.1, J4.3, U3.2 (GND), U4.2; also elsewhere on the board
unnamed: F1.1, R5.2, U4.3
unnamed: F1.2, J4.4

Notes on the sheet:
200V/V
62mR * I * 200v/v = 3.3V Imax = 266mA

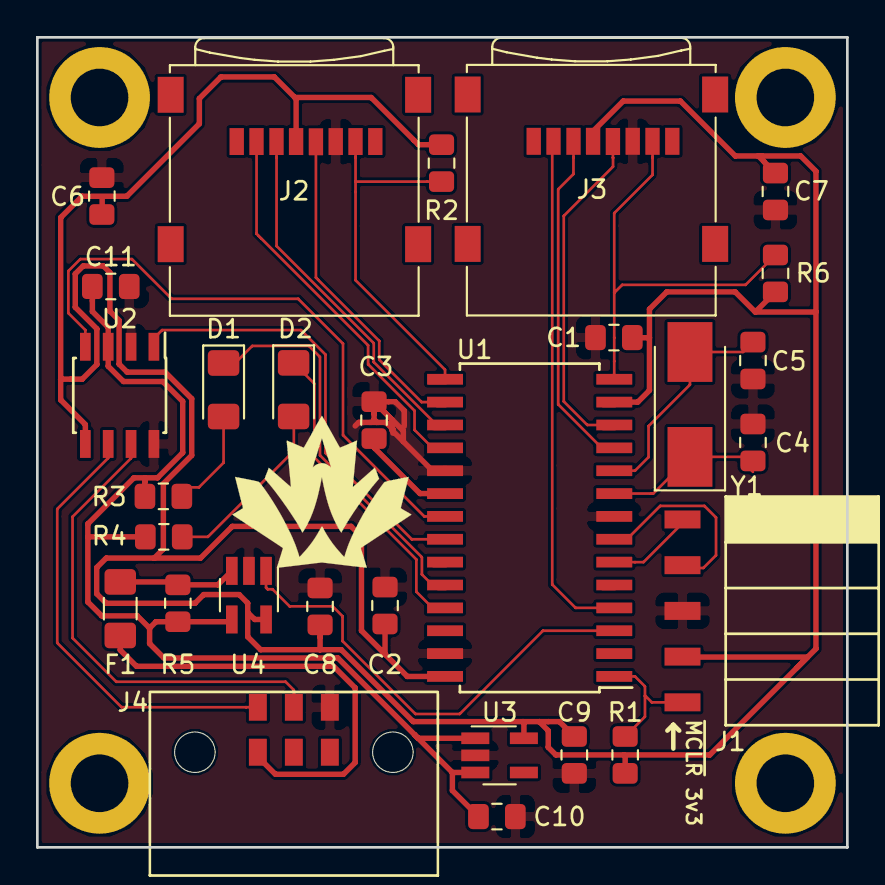
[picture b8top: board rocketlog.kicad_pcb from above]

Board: 2 copper layers, 45.0 x 45.0 mm, 29 parts (0 on the bottom side), 28 nets.
